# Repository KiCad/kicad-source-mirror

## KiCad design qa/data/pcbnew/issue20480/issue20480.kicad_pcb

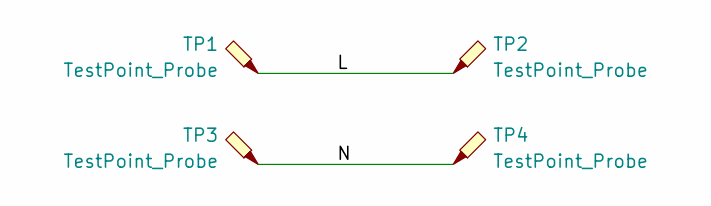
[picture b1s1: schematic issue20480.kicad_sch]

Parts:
TP1, TP2, TP3, TP4: TestPoint_Probe; TestPoint_Plated_Hole_D2.0mm

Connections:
/L: TP1.1, TP2.1
/N: TP3.1, TP4.1

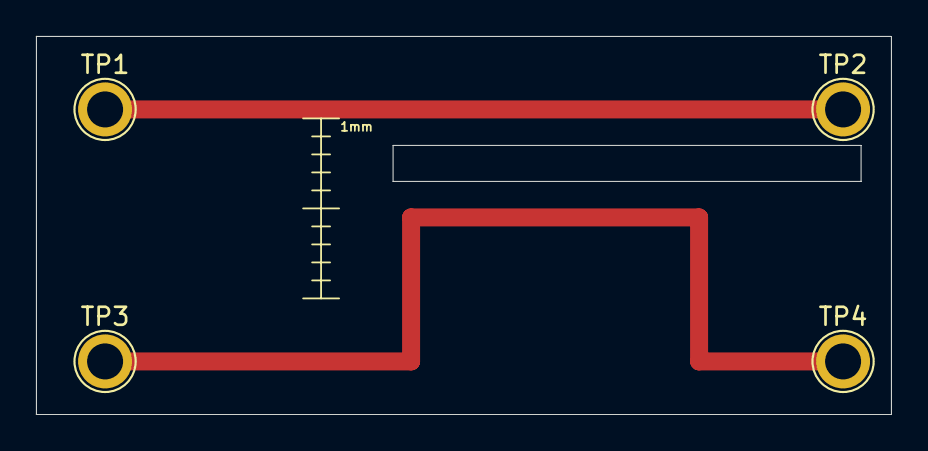
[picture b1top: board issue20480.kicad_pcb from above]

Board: 2 copper layers, 47.5 x 21.0 mm, 4 parts (0 on the bottom side), 2 nets.
